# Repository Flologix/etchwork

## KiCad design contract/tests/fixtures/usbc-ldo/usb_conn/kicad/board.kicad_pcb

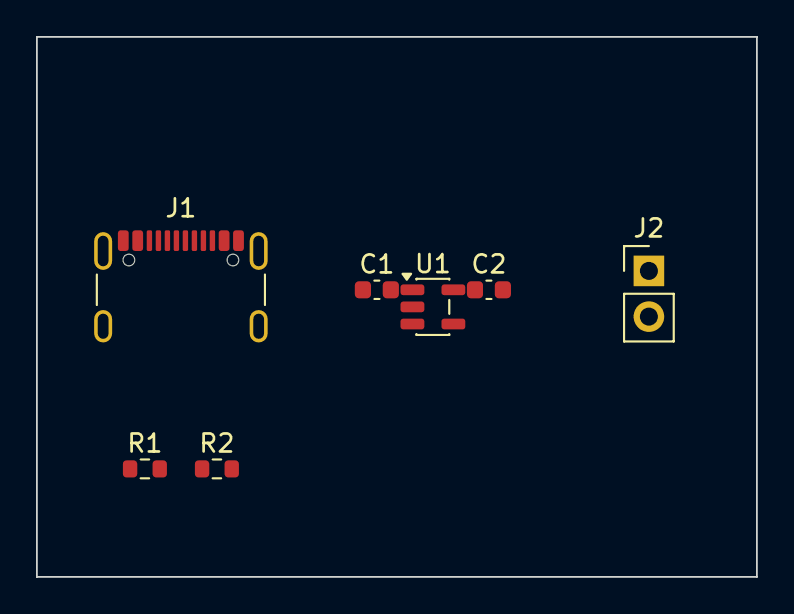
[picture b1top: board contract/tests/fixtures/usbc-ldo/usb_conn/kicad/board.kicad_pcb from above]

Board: 2 copper layers, 40.0 x 30.0 mm, 7 parts (0 on the bottom side), 5 nets, no tracks yet.

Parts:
C1, C2: 1u; C_0603_1608Metric
J1: USB_C_Receptacle_USB2.0_16P; USB_Micro-B_Molex-105017-0001
J2: Conn_01x02; PinHeader_1x02_P2.54mm_Vertical
R1, R2: 5.1k; R_0603_1608Metric
U1: AP2112K-3.3; SOT-23-5

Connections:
+3V3: C2.1, J2.1, U1.5 (VOUT)
CC1: J1.A5 (CC1), R1.1
CC2: J1.B5 (CC2), R2.1
GND: C1.1, C2.2, J1.A1 (GND), J1.A12 (GND), J1.B1 (GND), J1.B12 (GND), J1.SH (SHIELD), J2.2, R1.2, R2.2, U1.2 (GND)
VBUS: C1.2, J1.A4 (VBUS), J1.A9 (VBUS), J1.B4 (VBUS), J1.B9 (VBUS), U1.1 (VIN), U1.3 (EN)

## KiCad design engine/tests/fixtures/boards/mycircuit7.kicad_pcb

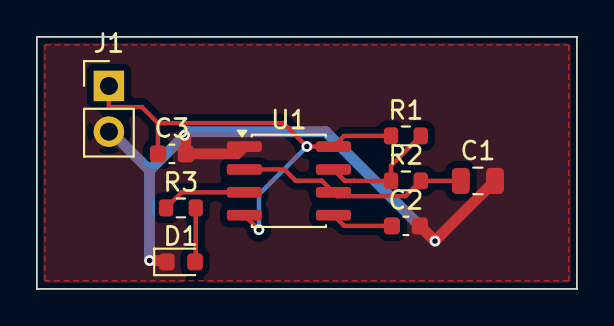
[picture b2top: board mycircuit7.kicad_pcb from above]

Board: 2 copper layers, 30.0 x 14.0 mm, 9 parts (0 on the bottom side), 7 nets.

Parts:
C1: 10uF; C_0805_2012Metric
C2: 10nF; C_0603_1608Metric
C3: 100nF; C_0603_1608Metric
D1: LED_RED; LED_0603_1608Metric
J1: PWR_IN; PinHeader_1x02_P2.54mm_Vertical
R1: 10k; R_0603_1608Metric
R2: 68k; R_0603_1608Metric
R3: 330R; R_0603_1608Metric
U1: NE555D; SOIC-8_3.9x4.9mm_P1.27mm

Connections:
CONT: C2.1, U1.5
DISCH: R1.2, R2.1, U1.7
GND: C1.2, C2.2, C3.2, D1.1, J1.2, U1.1
LED_A: D1.2, R3.2
OUT: R3.1, U1.3
THRESH: C1.1, R2.2, U1.2, U1.6
VCC_5V: C3.1, J1.1, R1.1, U1.4, U1.8

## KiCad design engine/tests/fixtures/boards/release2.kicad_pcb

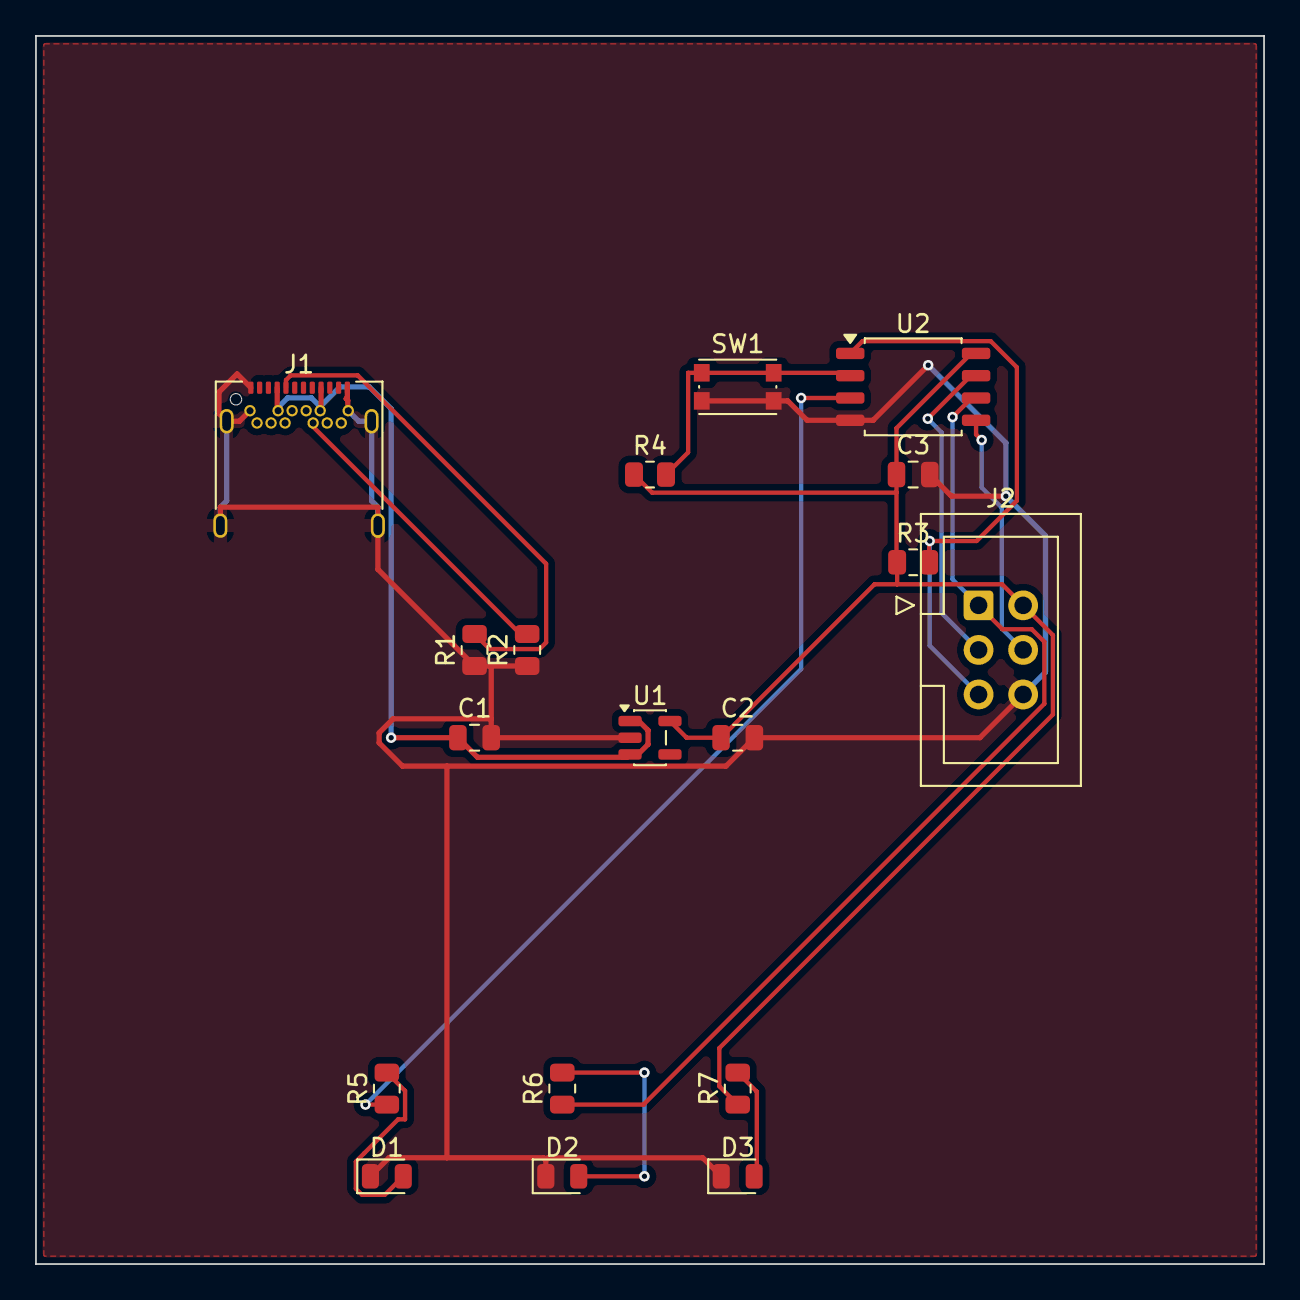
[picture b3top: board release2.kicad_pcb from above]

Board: 2 copper layers, 70.0 x 70.0 mm, 18 parts (0 on the bottom side), 14 nets.

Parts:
C1, C2: 10uF; C_0805_2012Metric
C3: 100nF; C_0805_2012Metric
D1, D2, D3: LED; LED_0805_2012Metric
J1: USB_C_Receptacle_PowerOnly_24P; USB_C_Receptacle_Amphenol_12401548E4-2A
J2: AVR-ISP-6; IDC-Header_2x03_P2.54mm_Vertical
R1, R2: 5.1k; R_0805_2012Metric
R3, R4: 10k; R_0805_2012Metric
R5, R6: 330; R_0805_2012Metric
R7: 1k; R_0805_2012Metric
SW1: SW_MEC_5E; SW_Push_1P1T_NO_CK_KMR2
U1: AP2112K-3.3; SOT-23-5
U2: ATtiny85-20S; SOIC-8_5.3x5.3mm_P1.27mm

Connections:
BUTTON: R4.2, SW1.1, U2.2
CC1: J1.A5, R1.2
CC2: J1.B5, R2.2
GND: C1.2, C2.2, C3.2, D1.1, D2.1, D3.1, J1.A1, J1.A12, J1.B1, J1.B12, J1.SH, J2.6, R1.1, R2.1, SW1.2, U1.2, U2.4
LED_A: R5.1, U2.3
MISO: J2.1, R6.1, U2.6
MOSI: J2.4, U2.5
unnamed: D1.2, R5.2
unnamed: D2.2, R6.2
unnamed: D3.2, R7.2
RESET: J2.5, R3.2, U2.1
SCK: J2.3, U2.7
VCC_3V3: C2.1, C3.1, J2.2, R3.1, R4.1, R7.1, U1.5, U2.8
VCC_5V: C1.1, J1.A4, J1.A9, J1.B4, J1.B9, U1.1, U1.3

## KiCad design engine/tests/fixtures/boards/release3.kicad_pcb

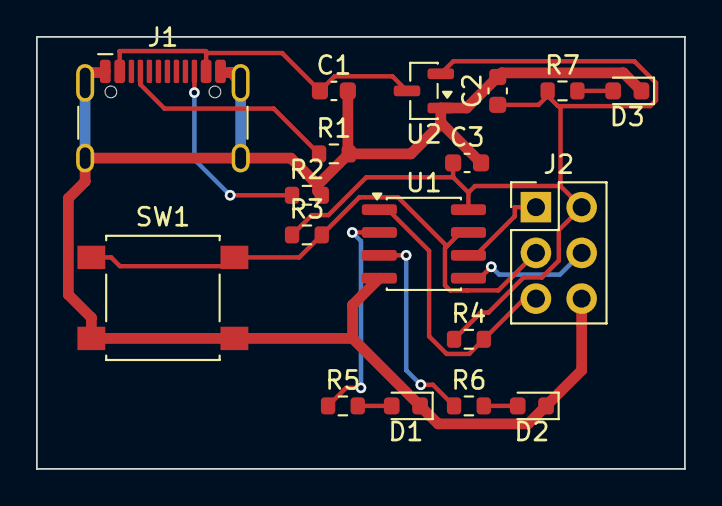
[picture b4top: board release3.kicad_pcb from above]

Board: 2 copper layers, 36.0 x 24.0 mm, 18 parts (0 on the bottom side), 14 nets.

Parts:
C1: 10uF; C_0603_1608Metric
C2: 1uF; C_0603_1608Metric
C3: 100nF; C_0603_1608Metric
D1: Red; LED_0603_1608Metric
D2, D3: Green; LED_0603_1608Metric
J1: USB_C_Receptacle_USB2.0_16P; USB_C_Receptacle_HCTL_HC-TYPE-C-16P-01A
J2: AVR-ISP-6; PinHeader_2x03_P2.54mm_Vertical
R1, R2: 5.1k; R_0603_1608Metric
R3, R4: 10k; R_0603_1608Metric
R5, R6: 330; R_0603_1608Metric
R7: 220; R_0603_1608Metric
SW1: SW_Push; SW_SPST_B3S-1000
U1: ATtiny85-20S; SOIC-8_3.9x4.9mm_P1.27mm
U2: MCP1700x-330xxTT; SOT-23

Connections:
CC1: J1.A5, R1.1
CC2: J1.B5, R2.1
GND: C1.2, C2.2, C3.2, D1.1, D2.1, D3.1, J1.A1, J1.A12, J1.B1, J1.B12, J1.SH, J2.6, R1.2, R2.2, SW1.2, U1.4, U2.1
LED1: R5.1, U1.2
LED1_R: D1.2, R5.2
LED2: R6.1, U1.3
LED2_R: D2.2, R6.2
MISO: J2.1, U1.6
MOSI: J2.4, U1.5
PWR_LED: D3.2, R7.2
RESET: J2.5, R4.2, U1.1
SCK_BTN: J2.3, R3.2, SW1.1, U1.7
VBUS_5V: C1.1, J1.A4, J1.A9, J1.B4, J1.B9, U2.3
VCC3V3: C2.1, C3.1, J2.2, R3.1, R4.1, R7.1, U1.8, U2.2

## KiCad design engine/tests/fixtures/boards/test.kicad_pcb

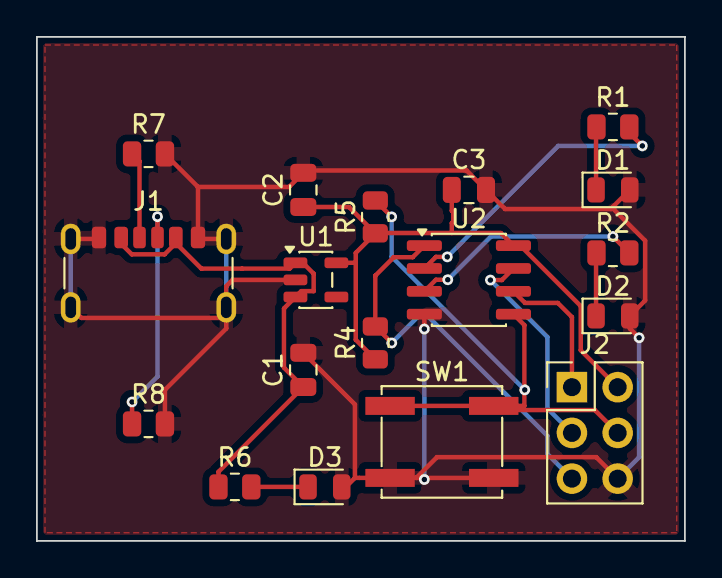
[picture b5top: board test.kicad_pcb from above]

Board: 2 copper layers, 36.0 x 28.0 mm, 18 parts (0 on the bottom side), 14 nets.

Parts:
C1, C2: 1uF; C_0805_2012Metric
C3: 100nF; C_0805_2012Metric
D1: RED; LED_0805_2012Metric
D2: GRN; LED_0805_2012Metric
D3: PWR; LED_0805_2012Metric
J1: USB-C 6P; USB_C_Receptacle_GCT_USB4125-xx-x_6P_TopMnt_Horizontal
J2: ISP; PinHeader_2x03_P2.54mm_Vertical
R1, R2: 330; R_0805_2012Metric
R4, R5: 10k; R_0805_2012Metric
R6: 470; R_0805_2012Metric
R7, R8: 5k1; R_0805_2012Metric
SW1: BTN; SW_SPST_EVQP0
U1: AP2112K-3.3; SOT-23-5
U2: ATtiny85-20SU; SOIC-8_3.9x4.9mm_P1.27mm

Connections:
CC1: J1.A5, R7.1
CC2: J1.B5, R8.1
GND: C1.2, C2.2, C3.2, D1.2, D2.2, D3.2, J1.A12, J1.B12, J1.SH, J2.6, R7.2, R8.2, SW1.2, U1.2, U2.4
ISP_MISO: J2.1, U2.6
ISP_MOSI: J2.4, R5.2, SW1.1, U2.5
ISP_RESET: J2.5, R4.2, U2.1
ISP_SCK: J2.3, U2.7
LED1: R1.2, U2.2
LED2: R2.2, U2.3
unnamed: D3.1, R6.2
unnamed: D1.1, R1.1
unnamed: D2.1, R2.1
VBUS: C1.1, J1.A9, J1.B9, R6.1, U1.1, U1.3
VCC3V3: C2.1, C3.1, J2.2, R4.1, R5.1, U1.5, U2.8

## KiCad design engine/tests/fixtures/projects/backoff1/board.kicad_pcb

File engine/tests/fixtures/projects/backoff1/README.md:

# board

A USB-C powered ATtiny85 LED blinker: plug it into any USB-C charger or port, the
5.1 k Rd pull-downs on CC1/CC2 tell the source to switch VBUS on, an AP2112K-3.3
LDO makes 3.3 V, and the ATtiny85 blinks two LEDs (PB3, PB4) while a user button
(PB2, with a 10 k pull-up) is available for mode changes. A yellow power LED
shows that 5 V is present. Board is 34 x 22 mm, two copper layers, with a GND
pour on both sides.

## Design notes

Generated facts are in the block below; everything here is my own reasoning about
the design, kept outside the generated block.

**Pin budget was the binding constraint.** The ATtiny85 has six GPIOs and the 2x3
Atmel ISP header takes four of them (PB0=MOSI, PB1=MISO, PB2=SCK, PB5=~RST),
leaving PB3/PB4 for the two blink LEDs and only PB2 for the button. PB2 is
therefore shared between the ISP clock and the button, and it is the pin that also
carries INT0, so the firmware can wake on a button press. The button is wired to
GND with an external 10 k pull-up (not a pull-down), so an idle button leaves the
SCK line high and does not fight the programmer; holding the button *while*
programming will corrupt the clock, so program with the button released. If a
future revision needs a dedicated button pin, move to an SOIC-14 AVR (ATtiny44/84)
or drop the ISP header in favour of a 3-pin debugWIRE pad.

**USB-C connector choice.** The first pass used the full 16-pad
`Connector:USB_C_Receptacle_USB2.0_16P` / HRO TYPE-C-31-M-12. Its KiCad footprint
puts all 16 contacts in a single row at 0.5 mm pitch, so the four VBUS pads are
boxed in by D+/D-/SBU pads that this board does not even use, and the autorouter
could not stitch VBUS pad-to-pad without breaking the 0.2 mm clearance (DRC kept
2 unconnected errors). Since the board carries no USB data, it now uses the
power-only Type-C receptacle (`USB_C_Receptacle_PowerOnly_6P` with footprint
`Connector_USB:USB_C_Receptacle_GCT_USB4125-xx-x_6P_TopMnt_Horizontal`, GCT
USB4125 series), whose row is 6 pads with ~1 mm of air between them. VBUS then
routes cleanly and the connector's dead data contacts are not on the board at all.
Trade-off: this board can never be re-used as a USB data device; if that matters,
go back to the 16P part and hand-route the VBUS stitching.

**CC resistors.** R1/R2 are 5.1 k each, one per CC pin to GND: that is the
spec-mandated Rd for a sink, and it is what makes a charger/host close its VBUS
switch. Without them a compliant USB-C source will not power the board at all.
The pair advertises default USB power (500 mA); this board draws roughly 15 mA.

**Power / passives.** C1 10 uF on the LDO input, C2 4.7 uF on its output (both
inside the AP2112's specified range, X5R 0805), C3 100 nF as the MCU decoupling
cap. The LDO's EN is strapped to VIN (pin 4 is the NC pad, left open). LED currents:
470 R on the 3.3 V blink LEDs (~2.8 mA) and 1 k on the 5 V power LED (~2-3 mA).
No input fuse or reverse/over-voltage protection: a USB-C source is current
limited by definition, but a mis-wired 5 V supply on the pad would reach the LDO
directly. There is also no ESD protection on the connector, which is acceptable
for a bench toy and not for a product.

**Layout.** Bands, bottom to top: the USB-C receptacle at the bottom-left edge
with the button and the ISP header along the same edge; the power chain (CC
pull-downs, input cap, LDO, output cap, pull-up) in the row directly above the
connector, so VBUS and 3.3 V leave the connector without crossing signals; the
MCU and its LED resistor/LED chains in the top two rows. The connector's shield
legs are NPTH and the router was kept clear of them. Track widths come from
`board.netclasses.json` (see the table below): VBUS and GND 0.6 mm, signals
0.25 mm. GND is poured on both layers, ~822 mm^2 of copper, with solid pour
connections where thermal relief would have starved a pad.

**DRC status: clean, 0 errors, 0 unconnected** on KiCad 10.0.5 with the JLCPCB
2-layer standard rules (default floors, nothing loosened). 22 warnings remain and
are deliberately not "fixed":
- `lib_footprint_issues` (17) - "the current configuration does not include the
  footprint library X". The container has no `fp-lib-table`, so KiCad cannot match
  the embedded footprints back to a library. The footprints themselves *are* in
  `board.kicad_pcb` and in the Gerbers, so the manufacturing data is complete.
- `silk_edge_clearance` (4) and `silk_overlap` (1) - reference designator text is
  clipped by the board edge (J2, U1) or touches a neighbouring part's silkscreen.
  Purely cosmetic; fixable by hiding or moving the fields in KiCad, which the
  SKiDL flow does not drive.

**How to rebuild.** `run_skidl` on `board.py` regenerates `board.net`; check it
against `expected.netlist.toml` with `check_netlist`; `classify_nets` writes
`board.netclasses.json`; `run_layout` with the positions used here reproduces the
board; `export_gerbers` writes `gerbers/`. Firmware is not part of this repo: any
ATtiny85 sketch that toggles PB3/PB4 and reads PB2 works, fuse-wise the default
8 MHz internal clock and RESET enabled are what this board assumes.

<!-- circuit:summary begin (generated by summarize_project; edits here are replaced) -->
## Parts

| Ref | Value | Footprint |
|---|---|---|
| C1 | 10uF | Capacitor_SMD:C_0805_2012Metric |
| C2 | 4.7uF | Capacitor_SMD:C_0805_2012Metric |
| C3 | 100nF | Capacitor_SMD:C_0805_2012Metric |
| D1 | LED Green | LED_SMD:LED_0805_2012Metric |
| D2 | LED Red | LED_SMD:LED_0805_2012Metric |
| D3 | LED Yellow | LED_SMD:LED_0805_2012Metric |
| J2 | AVR-ISP-6 | Connector_PinHeader_2.54mm:PinHeader_2x03_P2.54mm_Vertical |
| R1 | 5.1k | Resistor_SMD:R_0805_2012Metric |
| R2 | 5.1k | Resistor_SMD:R_0805_2012Metric |
| R3 | 10k | Resistor_SMD:R_0805_2012Metric |
| R4 | 470 | Resistor_SMD:R_0805_2012Metric |
| R5 | 470 | Resistor_SMD:R_0805_2012Metric |
| R6 | 1k | Resistor_SMD:R_0805_2012Metric |
| S1 | SW_MEC_5G | Button_Switch_THT:SW_PUSH_6mm |
| U1 | USB_C_Receptacle_GCT_USB4125_6P | Connector_USB:USB_C_Receptacle_GCT_USB4125-xx-x_6P_TopMnt_Horizontal |
| U2 | AP2112K-3.3 | Package_TO_SOT_SMD:SOT-23-5 |
| U3 | ATtiny85-20S | Package_SO:SOIC-8_3.9x4.9mm_P1.27mm |

## Net classes

| Net | Class | Tier | Width (mm) | Source | Status |
|---|---|---|---|---|---|
| +3V3 | power_logic | lt_0_5a | 0.25 | jev | accepted |
| CC1 | power_high_current | lt_0_5a | 0.25 | jev (resolver held) | needs_review |
| CC2 | power_high_current | lt_0_5a | 0.25 | jev (resolver held) | needs_review |
| GND | ground | - | 0.6 | rule | accepted |
| ISP_MISO | signal | lt_0_5a | 0.25 | jev | accepted |
| ISP_MOSI | signal | lt_0_5a | 0.25 | jev | accepted |
| ISP_RST | signal | lt_0_5a | 0.25 | jev | accepted |
| ISP_SCK | signal | lt_0_5a | 0.25 | jev | accepted |
| LED1 | signal | lt_0_5a | 0.25 | jev | accepted |
| LED1_R | signal | lt_0_5a | 0.25 | jev | accepted |
| LED2 | signal | lt_0_5a | 0.25 | jev | accepted |
| LED2_R | signal | lt_0_5a | 0.25 | jev | accepted |
| PWR_LED | signal | lt_0_5a | 0.25 | jev | accepted |
| VBUS_5V | power_high_current | 0_5a_to_2a | 0.6 | jev (resolver held) | needs_review |

## Nets awaiting your decision

- **CC1**: resolver held: lowers jev's rating: signal lt_0_5a (power_high_current net accepted as signal); sized 0.25 mm from jev's lt_0_5a
- **CC2**: resolver held: lowers jev's rating: signal lt_0_5a (power_high_current net accepted as signal); sized 0.25 mm from jev's lt_0_5a
- **VBUS_5V**: resolver held: lowers jev's rating: power_high_current lt_0_5a (tier lt_0_5a below jev's 0_5a_to_2a); sized 0.8 mm from jev's 0_5a_to_2a
- **GND**: routed at 0.6 mm, pad-limited, below the 0.8 mm tier
- **VBUS_5V**: routed at 0.6 mm, pad-limited, below the 0.8 mm tier

## Board

Status: DRC clean

- File: `board.kicad_pcb`
- Footprints: 17
- Track segments: 59 on B.Cu, 101 on F.Cu
- Outline (Edge.Cuts): yes
- Copper pours: 2, all filled
- DRC: 0 error(s), 22 warning(s)
- Gerbers: board-B_Cu.gbl, board-B_Mask.gbs, board-B_Paste.gbp, board-B_Silkscreen.gbo, board-Edge_Cuts.gm1, board-F_Cu.gtl, board-F_Mask.gts, board-F_Paste.gtp, board-F_Silkscreen.gto, board-NPTH-drl_map.gbr, board-NPTH.drl, board-PTH-drl_map.gbr, board-PTH.drl, board-job.gbrjob
<!-- circuit:summary end -->

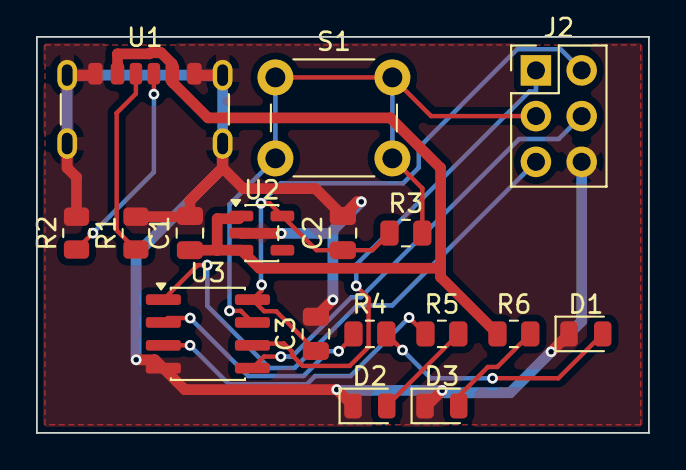
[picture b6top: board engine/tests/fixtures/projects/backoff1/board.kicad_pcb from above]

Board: 2 copper layers, 34.0 x 22.0 mm, 17 parts (0 on the bottom side), 14 nets.

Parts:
C1: 10uF; C_0805_2012Metric
C2: 4.7uF; C_0805_2012Metric
C3: 100nF; C_0805_2012Metric
D1: LED Green; LED_0805_2012Metric
D2: LED Red; LED_0805_2012Metric
D3: LED Yellow; LED_0805_2012Metric
J2: AVR-ISP-6; PinHeader_2x03_P2.54mm_Vertical
R1, R2: 5.1k; R_0805_2012Metric
R3: 10k; R_0805_2012Metric
R4, R5: 470; R_0805_2012Metric
R6: 1k; R_0805_2012Metric
S1: SW_MEC_5G; SW_PUSH_6mm
U1: USB_C_Receptacle_GCT_USB4125_6P; USB_C_Receptacle_GCT_USB4125-xx-x_6P_TopMnt_Horizontal
U2: AP2112K-3.3; SOT-23-5
U3: ATtiny85-20S; SOIC-8_3.9x4.9mm_P1.27mm

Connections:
+3V3: C2.1, C3.1, J2.2, R3.1, U2.5, U3.8
CC1: R1.1, U1.A5
CC2: R2.1, U1.B5
GND: C1.2, C2.2, C3.2, D1.1, D2.1, D3.1, J2.6, R1.2, R2.2, U1.A12, U1.B12, U1.SH, U2.2, U3.4
ISP_MISO: J2.1, U3.6
ISP_MOSI: J2.4, U3.5
ISP_RST: J2.5, U3.1
ISP_SCK: J2.3, R3.2, S1.1, S1.2, U3.7
LED1: R4.1, U3.2
LED1_R: D1.2, R4.2
LED2: R5.1, U3.3
LED2_R: D2.2, R5.2
PWR_LED: D3.2, R6.2
VBUS_5V: C1.1, R6.1, U1.A9, U1.B9, U2.1, U2.3

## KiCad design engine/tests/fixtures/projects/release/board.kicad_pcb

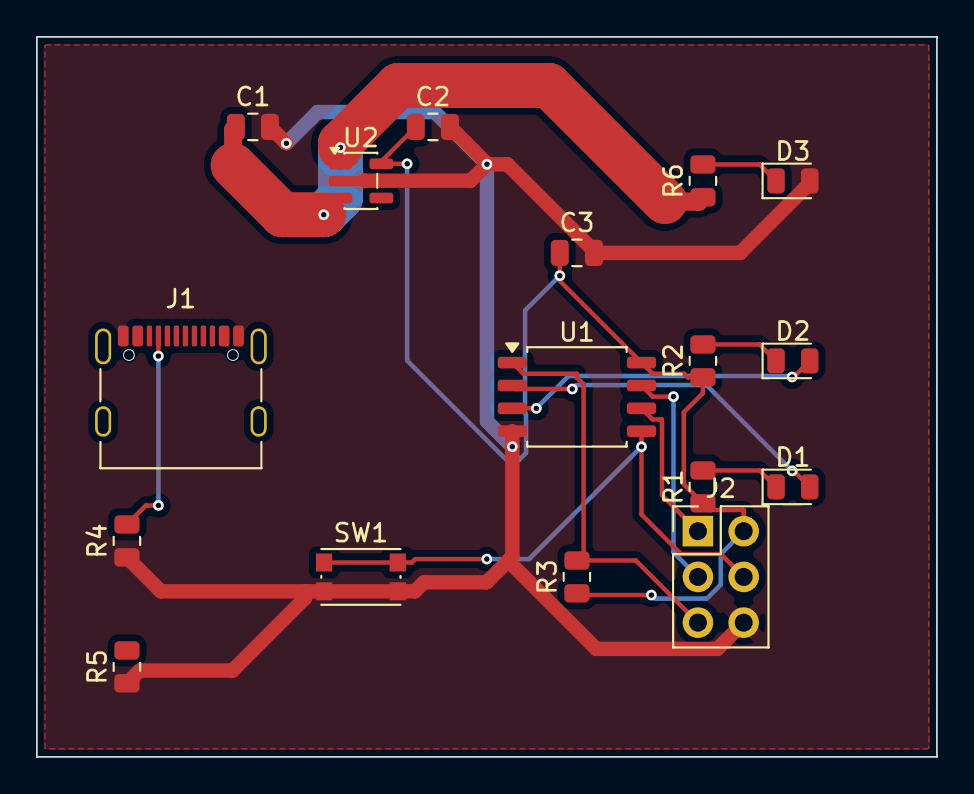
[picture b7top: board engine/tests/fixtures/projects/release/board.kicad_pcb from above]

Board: 2 copper layers, 50.0 x 40.0 mm, 17 parts (0 on the bottom side), 14 nets.

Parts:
C1: 10u; C_0805_2012Metric
C2: 22u; C_0805_2012Metric
C3: 100n; C_0805_2012Metric
D1, D2, D3: LED; LED_0805_2012Metric
J1: USB_C_Receptacle_PowerOnly_24P; USB_C_Receptacle_Palconn_UTC16-G
J2: AVR-ISP-6; PinHeader_2x03_P2.54mm_Vertical
R1, R2: 330; R_0805_2012Metric
R3: 10k; R_0805_2012Metric
R4, R5: 5.1k; R_0805_2012Metric
R6: 1k; R_0805_2012Metric
SW1: SW_Push; SW_Push_1P1T_NO_CK_KMR2
U1: ATtiny85-20S; SOIC-8_5.3x5.3mm_P1.27mm
U2: AP2112K-3.3; SOT-23-5

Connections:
CC1: J1.A5, R4.2
CC2: J1.B5, R5.2
GND: C1.2, C2.2, C3.2, D3.2, J1.A1, J1.A12, J1.B1, J1.B12, J2.6, R4.1, R5.1, SW1.2, U1.4, U2.2
LED_A: D1.2, U1.2
LED_B: D2.2, U1.3
MISO: J2.1, U1.6
MOSI: J2.4, SW1.1, U1.5
unnamed: D3.1, R6.2
NET_LED_A: D1.1, R1.2
NET_LED_B: D2.1, R2.2
RESET: J2.5, R3.2, U1.1
SCK: J2.3, U1.7
VBUS: C1.1, J1.A4, J1.A9, J1.B4, J1.B9, R6.1, U2.1, U2.3
VCC_3V3: C2.1, C3.1, J2.2, R1.1, R2.1, R3.1, U1.8, U2.5
